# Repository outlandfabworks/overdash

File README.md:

# Overdash

Open-source digital dashboard for Raspberry Pi. Most commercial Pi-based dash solutions lock you into a single ECU brand and require paid third-party software licenses. Overdash doesn't: it speaks **J1939 CAN, OBD-II K-line, ELM327, CAN OBD, GPS, and GPIO** natively, so it works with engine swaps, custom builds, and vehicles that commercial options simply don't support.

A Python async backend reads from any combination of those sources simultaneously and streams everything over WebSocket to a Chromium kiosk frontend. Gauges are rendered on canvas, and the layout is fully editable in-browser with a visual no-code editor. No paid software required.

Built for a TDI-swapped Land Rover Discovery (J1939 engine + CompuShift Sport TCM + ZF4HP22EH), but config-driven; no code changes needed to adapt it to another vehicle.

---

## Features

- **Multiple data sources**: J1939 CAN, CompuShift TCM, OBD-II (K-line and ELM327), CAN OBD, Megasquirt/Speeduino USB serial, GPS (NMEA), analog ADC, frequency counter, GPIO inputs, and a mock source for development without hardware
- **Visual no-code layout editor**: drag to move, resize handles, properties panel for zones/thresholds/colors, gauge palette, theme picker, save to server or export JSON
- **Gauge types**: circular sweep (tach, speedo), vertical/horizontal bar, large numeric with value mapping, indicator lights, warning light strip with DTC panel
- **DTC monitoring**: Mode 03 (stored) + Mode 07 (pending) codes, MIL status, tap any active warning light to open the fault code panel
- **Odometer**: integrates vehicle speed into a persisted lifetime total and resettable trip counter
- **PWA**: add to home screen on a tablet for fullscreen landscape kiosk mode
- **Auth-protected HTTP API**: layout save/load, signal snapshot, trip reset, odometer set, per-source simulation mode

---

## Quick start

```bash
# Clone
git clone https://github.com/outlandfabworks/overdash.git
cd overdash

# Create a virtual environment and install dependencies
python3 -m venv .venv
.venv/bin/pip install -r requirements.txt

# Test with the mock vehicle source (no hardware required)
.venv/bin/python -m backend.main configs/vehicles/mock.yaml

# Open http://localhost:8080 in a browser
```

For full installation on a Raspberry Pi (CAN setup, systemd service, Chromium kiosk), see [INSTALL.md](INSTALL.md).

---

## Project structure

```
backend/
  main.py                     Entry point: wires sources, processors, servers
  data_bus.py                 In-memory signal store with asyncio pub/sub
  config.py                   YAML loader
  sources/
    base.py                   Abstract DataSource
    can_j1939.py              J1939 PGN/SPN decoder (python-can)
    can_compushift.py         CompuShift Sport TCM CAN messages
    can_obd.py                OBD-II over CAN (ISO 15765-4)
    obd_kline.py              ISO 9141-2 / KWP2000 K-line poller
    elm327.py                 ELM327 USB/Bluetooth OBD adapter
    megasquirt.py             Megasquirt 1/2/3 and Speeduino USB serial
    gps_nmea.py               GPS via NMEA serial stream
    analog_adc.py             Analog voltage/sensor via SPI ADC (MCP3xxx)
    frequency_counter.py      RPM/frequency via GPIO pulse counting
    gpio_inputs.py            Overdash Input HAT (turn signals, lights, reverse)
    mock_vehicle.py           Simulated signals for dev/testing
  processors/
    odometer.py               Integrates vehicle_speed → odometer + trip signals
  server/
    websocket.py              WebSocket broadcast server (30 Hz)
    http_api.py               HTTP API + frontend file serving (port 8080)

frontend/
  index.html                  Shell: loads layout, connects WebSocket
  manifest.json               PWA manifest (fullscreen, landscape)
  js/
    ws_client.js              WebSocket client with auto-reconnect
    layout.js                 CSS grid layout builder from JSON config
    gauge_registry.js         Plugin registry for gauge types
    gauges/
      base.js                 BaseGauge (canvas helpers, zone color lookup)
      circular.js             Circular/sweep gauge (tach, speedo)
      bar.js                  Vertical/horizontal bar gauge
      numeric.js              Large-number display with value_map support
      indicator.js            Single signal indicator light
      lights.js               Warning light strip with DTC panel
      light_icons.js          SVG icon definitions for warning lights
  editor/
    editor.js                 Visual layout editor (drag, resize, save)
    editor.css                Editor chrome and panel styles
    palette.js                Gauge palette sidebar
    properties.js             Gauge properties panel
    drag_grid.js              Grid snap and drag logic
  css/
    base.css                  Layout chrome, status bar
    themes/dark.css           Dark theme CSS variables
    themes/light.css          Light theme CSS variables

configs/
  vehicles/
    tdi_discovery.yaml        TDI Land Rover: J1939 + CompuShift + K-line
    generic_modern.yaml       Modern petrol/diesel: ELM327 or CAN OBD
    generic_obd2.yaml         Older OBD-II vehicle: K-line only
    offroad_expedition.yaml   Off-road build with GPS + ADC sensors
    mock.yaml                 Mock source: no hardware needed
  layouts/
    tdi_discovery.json        Default layout for the TDI Discovery

hardware/
  overdash-input-hat/          KiCad schematic and PCB for the GPIO input HAT
```

---

## Signal flow

```
Hardware  →  Source._read_loop()  →  DataBus.publish(name, value, unit)
                                           │
                                   OdometerProcessor (vehicle_speed → odometer/trip)
                                           │
                                   WebSocketServer (batches at 30 Hz)
                                           │
                                   Browser WSClient
                                           │
                                   LayoutManager.update(signals)
                                           │
                                   Gauge.draw(value)  →  <canvas>
```

---

## Adding a gauge type

1. Create `frontend/js/gauges/my_gauge.js` extending `BaseGauge`, implement `draw(value)`.
2. Register it in `index.html`: `GaugeRegistry.register('my_gauge', MyGauge)`.
3. Add a gauge entry in the layout JSON with `"type": "my_gauge"`.

## Adding a data source

1. Create `backend/sources/my_source.py` extending `BaseSource`, implement `_read_loop()`.
2. Register it in `backend/main.py`: `_SOURCE_TYPES['my_source'] = MySource`.
3. Add a source entry in the vehicle YAML with `type: my_source`.

---

## TDI Discovery: signal reference

| Signal | Source | Notes |
|--------|--------|-------|
| `engine_rpm` | J1939 PGN 61444 SPN 190 | EEC1 |
| `coolant_temp` | J1939 PGN 65262 | ET1 |
| `intake_map` | K-line PID 0x0B | Absolute kPa (doubles as boost) |
| `vehicle_speed` | J1939 PGN 65265 | CCVS1 |
| `trans_current_gear_label` | CompuShift CAN 0x3E0 | P/R/N/D/3/2/1 |
| `trans_tcc_lockup` | CompuShift CAN 0x3E0 | 0 = open, 1 = locked |
| `trans_temp` | CompuShift CAN 0x3E1 | °C |
| `battery_voltage` | J1939 PGN 65271 | VEP1 |
| `odometer` | Processor | Persisted lifetime km |
| `trip` | Processor | Resettable trip km |

## CompuShift Sport CAN IDs

Default map derived from community reverse-engineering (Sport firmware ≥ 2.x).
Override via `messages:` in the vehicle YAML if your TCM uses different IDs.

| CAN ID | Content |
|--------|---------|
| 0x3E0 | Current gear, target gear, TCC status, shift mode |
| 0x3E1 | Trans temp |
| 0x3E2 | Line pressure, error codes |

---

## License

MIT. See [LICENSE](LICENSE). Third-party license notices in [THIRD_PARTY_LICENSES.md](THIRD_PARTY_LICENSES.md).

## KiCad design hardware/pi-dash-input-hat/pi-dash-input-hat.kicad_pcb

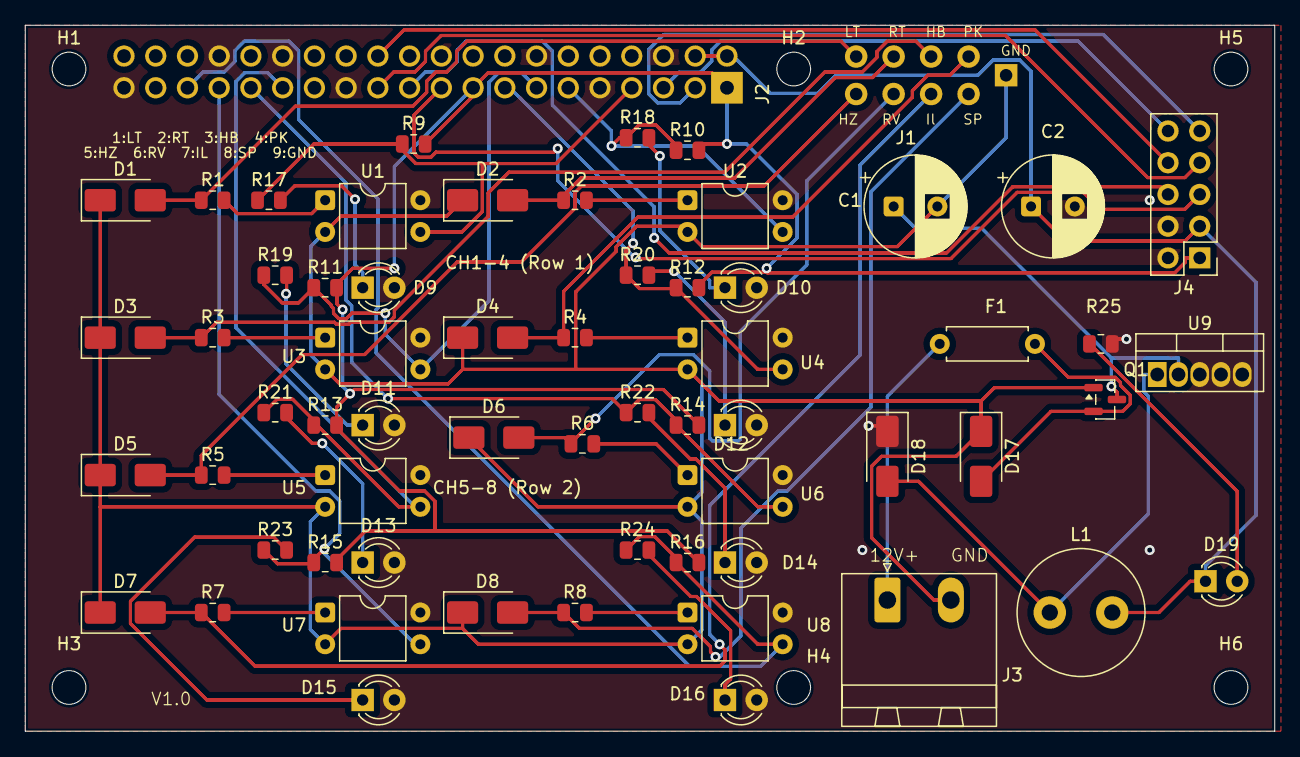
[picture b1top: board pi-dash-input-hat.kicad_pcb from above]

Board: 2 copper layers, 100.0 x 56.5 mm, 68 parts (0 on the bottom side), 47 nets.

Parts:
C1: 220u/35V; CP_Radial_D8.0mm_P3.50mm
C2: 220u/10V; CP_Radial_D8.0mm_P3.50mm
D1, D2, D3, D4, D5, D6, D7, D8: SMAJ15A; D_SMA
D9, D10, D11, D12, D13, D14, D15, D16, D19: LED_GRN; LED_D3.0mm
D17: SMAJ36A; D_SMA
D18: SB360; D_SMA
F1: 2.5A_Poly; R_Axial_DIN0207_L6.3mm_D2.5mm_P7.62mm_Horizontal
H1, H2, H3, H4, H5, H6: MountingHole_2.7mm_M2.5
J1: Molex_MicroFit3_9pin; PinHeader_1x09_P2.54mm_Vertical
J2: GPIO_2x20; PinHeader_2x20_P2.54mm_Vertical
J3: 12V_PWR_IN; PhoenixContact_MSTBA_2,5_2-G-5,08_1x02_P5.08mm_Horizontal
J4: Sensor_Connector; PinHeader_2x05_P2.54mm_Vertical
L1: 100u/3A; L_Radial_D10.0mm_P5.00mm_Fastron_07P
Q1: DMG2305UX; SOT-23
R1, R2, R3, R4, R5, R6, R7, R8: 560; R_0805_2012Metric
R9, R10, R11, R12, R13, R14, R15, R16: 10k; R_0805_2012Metric
R17, R18, R19, R20, R21, R22, R23, R24, R25: 1k; R_0805_2012Metric
U1, U2, U3, U4, U5, U6, U7, U8: PC817; DIP-4_W7.62mm
U9: LM2596-5.0; TO-220-5_Vertical

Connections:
12V_BATT: F1.1, J3.1
12V_CLEAN: D17.2, F1.2, Q1.2
+3V3: J2.1, J2.17, J4.1, R9.2, R10.2, R11.2, R12.2, R13.2, R14.2, R15.2, R16.2
+5V: C2.1, D19.1, J2.2, J2.4, J4.3, L1.2
CH1_LED: D9.1 (A), R17.2
CH1_MID: R1.2, U1.1 (A)
CH2_LED: D10.1 (A), R18.2
CH2_MID: R2.2, U2.1 (A)
CH3_LED: D11.1 (A), R19.2
CH3_MID: R3.2, U3.1 (A)
CH4_LED: D12.1 (A), R20.2
CH4_MID: R4.2, U4.1 (A)
CH5_LED: D13.1 (A), R21.2
CH5_MID: R5.2, U5.1 (A)
CH6_LED: D14.1 (A), R22.2
CH6_MID: R6.2, U6.1 (A)
CH7_LED: D15.1 (A), R23.2
CH7_MID: R7.2, U7.1 (A)
CH8_LED: D16.1 (A), R24.2
CH8_MID: R8.2, U8.1 (A)
GND: C2.2, D9.2 (K), D10.2 (K), D11.2 (K), D12.2 (K), D13.2 (K), D14.2 (K), D15.2 (K), D16.2 (K), D18.1, J2.6, J2.9, J2.14, J2.20, J2.25, J2.30, J2.34, J2.39, J4.2, J4.4, R25.2, U1.4 (E), U2.4 (E), U3.4 (E), U4.4 (E), U5.4 (E), U6.4 (E), U7.4 (E), U8.4 (E), U9.3, U9.4, U9.5
GND_CAR: C1.2, D1.1 (A), D2.1 (A), D3.1 (A), D4.1 (A), D5.1 (A), D6.1 (A), D7.1 (A), D8.1 (A), D17.1, J1.9, J3.2, Q1.1, U1.2 (K), U2.2 (K), U3.2 (K), U4.2 (K), U5.2 (K), U6.2 (K), U7.2 (K), U8.2 (K)
GPIO2: J2.3, J4.9
GPIO3: J2.5, J4.10
GPIO4: J2.7, R9.1, R17.1, U1.3 (C)
GPIO5: J2.29, R13.1, R21.1, U5.3 (C)
GPIO6: J2.31, R14.1, R22.1, U6.3 (C)
GPIO8: J2.24, J4.8
GPIO9: J2.21, J4.6
GPIO10: J2.19, J4.5
GPIO11: J2.23, J4.7
GPIO13: J2.33, R15.1, R23.1, U7.3 (C)
GPIO17: J2.11, R10.1, R18.1, U2.3 (C)
GPIO19: J2.35, R16.1, R24.1, U8.3 (C)
GPIO22: J2.15, R12.1, R20.1, U4.3 (C)
GPIO27: J2.13, R11.1, R19.1, U3.3 (C)
IN1_LT: D1.2 (K), J1.1, R1.1
IN2_RT: D2.2 (K), J1.2, R2.1
IN3_HB: D3.2 (K), J1.3, R3.1
IN4_PK: D4.2 (K), J1.4, R4.1
IN5_HZ: D5.2 (K), J1.5, R5.1
IN6_RV: D6.2 (K), J1.6, R6.1
IN7_IL: D7.2 (K), J1.7, R7.1
IN8_SP: D8.2 (K), J1.8, R8.1
LED_PWR: D19.2, R25.1
SW_NODE: D18.2, L1.1, U9.1
VIN_BUCK: C1.1, Q1.3, U9.2

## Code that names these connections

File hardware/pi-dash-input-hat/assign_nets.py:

import pcbnew

BOARD_FILE = '/home/zach/Documents/pi-dash/hardware/pi-dash-input-hat/pi-dash-input-hat.kicad_pcb'
board = pcbnew.LoadBoard(BOARD_FILE)

_net_cache = {}

def get_or_create_net(name):
    if name in _net_cache:
        return _net_cache[name]
    net = pcbnew.NETINFO_ITEM(board, name)
    board.Add(net)
    _net_cache[name] = net
    return net

def find_pad(fp, num):
    for pad in fp.Pads():
        if pad.GetNumber() == str(num):
            return pad
    return None

def assign(ref, pad_num, net_name):
    fp = board.FindFootprintByReference(ref)
    if not fp:
        print(f"FP not found: {ref}")
        return
    pad = find_pad(fp, pad_num)
    if not pad:
        print(f"Pad '{pad_num}' not found on {ref}")
        return
    pad.SetNet(get_or_create_net(net_name))

# Create all nets up front
for name in [
    'GND', 'GND_CAR', '+3V3', '+5V',
    'IN1_LT', 'IN2_RT', 'IN3_HB', 'IN4_PK',
    'IN5_HZ', 'IN6_RV', 'IN7_IL', 'IN8_SP',
    'GPIO4', 'GPIO5', 'GPIO6', 'GPIO13',
    'GPIO17', 'GPIO19', 'GPIO22', 'GPIO27',
    # Power section nets
    '12V_BATT', '12V_CLEAN', 'VIN_BUCK', 'SW_NODE', 'LED_PWR',
] + [f'CH{n}_MID' for n in range(1, 9)] \
  + [f'CH{n}_LED' for n in range(1, 9)]:
    get_or_create_net(name)

# Per-channel: D_TVS, R_560, U_PC817, R_pullup_10k, R_led_1k, D_LED, IN_net, GPIO_net
channels = [
    ('D1','R1', 'U1','R9', 'R17','D9',  'IN1_LT','GPIO4'),
    ('D2','R2', 'U2','R10','R18','D10', 'IN2_RT','GPIO17'),
    ('D3','R3', 'U3','R11','R19','D11', 'IN3_HB','GPIO27'),
    ('D4','R4', 'U4','R12','R20','D12', 'IN4_PK','GPIO22'),
    ('D5','R5', 'U5','R13','R21','D13', 'IN5_HZ','GPIO5'),
    ('D6','R6', 'U6','R14','R22','D14', 'IN6_RV','GPIO6'),
    ('D7','R7', 'U7','R15','R23','D15', 'IN7_IL','GPIO13'),
    ('D8','R8', 'U8','R16','R24','D16', 'IN8_SP','GPIO19'),
]

for i, (dn, rn, un, rpn, rln, dln, in_net, gpio) in enumerate(channels):
    ch   = i + 1
    mid  = f'CH{ch}_MID'
    led  = f'CH{ch}_LED'

    # TVS diode (SMAJ15A, D_SMA): pad 1 = A → car GND, pad 2 = K → input signal
    assign(dn, '1', 'GND_CAR')
    assign(dn, '2', in_net)

    # 560Ω input resistor (R_0805): pad 1 → input signal, pad 2 → opto input
    assign(rn, '1', in_net)
    assign(rn, '2', mid)

    # PC817 optocoupler (DIP-4):
    #   pin 1 A  → opto input (after R560)
    #   pin 2 K  → car GND
    #   pin 3 C  → GPIO / pull-up node
    #   pin 4 E  → Pi GND
    assign(un, '1', mid)
    assign(un, '2', 'GND_CAR')
    assign(un, '3', gpio)
    assign(un, '4', 'GND')

    # 10kΩ pull-up (R_0805): pad 1 → GPIO node, pad 2 → +3V3
    assign(rpn, '1', gpio)
    assign(rpn, '2', '+3V3')

    # 1kΩ LED resistor (R_0805): pad 1 → GPIO node, pad 2 → LED anode
    assign(rln, '1', gpio)
    assign(rln, '2', led)

    # Status LED (LED_D3.0mm): pad 1 A → LED anode, pad 2 K → Pi GND
    assign(dln, '1', led)
    assign(dln, '2', 'GND')

# J1 — 9-pin Molex: pads 1-8 = input signals, pad 9 = GND_CAR
for i, net in enumerate(['IN1_LT','IN2_RT','IN3_HB','IN4_PK',
                          'IN5_HZ','IN6_RV','IN7_IL','IN8_SP']):
    assign('J1', str(i + 1), net)
assign('J1', '9', 'GND_CAR')

# J2 — 2×20 Pi GPIO header (pad numbers = physical Pi pin numbers)
j2 = {
     1: '+3V3',   2: '+5V',    3: 'GPIO2',  4: '+5V',
     5: 'GPIO3',  6: 'GND',    7: 'GPIO4',  8: 'GPIO14',
     9: 'GND',   10: 'GPIO15', 11: 'GPIO17',12: 'GPIO18',
    13: 'GPIO27', 14: 'GND',   15: 'GPIO22',16: 'GPIO23',
    17: '+3V3',  18: 'GPIO24', 19: 'GPIO10',20: 'GND',
    21: 'GPIO9', 22: 'GPIO25', 23: 'GPIO11',24: 'GPIO8',
    25: 'GND',   26: 'GPIO7',  27: 'GPIO0', 28: 'GPIO1',
    29: 'GPIO5', 30: 'GND',   31: 'GPIO6', 32: 'GPIO12',
    33: 'GPIO13',34: 'GND',   35: 'GPIO19',36: 'GPIO16',
    37: 'GPIO26',38: 'GPIO20', 39: 'GND',  40: 'GPIO21',
}
for pad_num, net_name in j2.items():
    assign('J2', str(pad_num), net_name)

# ── Power section ─────────────────────────────────────────────────────────────
# J3 — 2-pin Phoenix screw terminal (12V input + GND_CAR)
assign('J3', '1', '12V_BATT')
assign('J3', '2', 'GND_CAR')

# F1 — series polyfuse (2.5A resettable)
assign('F1', '1', '12V_BATT')
assign('F1', '2', '12V_CLEAN')

# D17 — SMAJ36A TVS clamp (K on rail, A to car GND)
assign('D17', '1', 'GND_CAR')   # Anode
assign('D17', '2', '12V_CLEAN') # Cathode

# Q1 — DMG2305UX P-ch MOSFET reverse-polarity protection (SOT-23)
# Pad 1=G, 2=S, 3=D  (G→GND_CAR keeps MOSFET on; reversed polarity turns it off)
assign('Q1', '1', 'GND_CAR')    # Gate  → GND_CAR
assign('Q1', '2', '12V_CLEAN')  # Source → post-fuse rail
assign('Q1', '3', 'VIN_BUCK')   # Drain  → U9 VIN / C1 +

# C1 — 220µF/35V bulk input capacitor
assign('C1', '1', 'VIN_BUCK')   # +
assign('C1', '2', 'GND_CAR')    # −

# U9 — LM2596-5.0 buck converter (TO-220-5)
# Physical LM2596 pins: 1=OUT(switch), 2=VIN, 3=GND, 4=FB(fixed), 5=/ON-OFF
assign('U9', '1', 'SW_NODE')    # Switch output
assign('U9', '2', 'VIN_BUCK')   # VIN
assign('U9', '3', 'GND')        # GND (also exposed tab)
assign('U9', '4', 'GND')        # FB fixed internally; tie /ON-OFF to GND = always on
assign('U9', '5', 'GND')        # /ON-OFF → GND (always enabled)

# D18 — SB360 Schottky freewheeling diode (K toward switch node, A to GND)
assign('D18', '1', 'GND')       # Anode
assign('D18', '2', 'SW_NODE')   # Cathode → switch node

# L1 — 100µH/3A output inductor
assign('L1', '1', 'SW_NODE')    # pin 1 → switch node
assign('L1', '2', '+5V')        # pin 2 → +5V output

# C2 — 220µF/10V output filter capacitor
assign('C2', '1', '+5V')        # +
assign('C2', '2', 'GND')        # −

# D19 — green power LED (A→+5V, K→LED_PWR node)
assign('D19', '1', '+5V')       # Anode
assign('D19', '2', 'LED_PWR')   # Cathode → R25

# R25 — 1kΩ LED current limiter
assign('R25', '1', 'LED_PWR')   # → D19 cathode
assign('R25', '2', 'GND')       # → GND

board.Save(BOARD_FILE)
print("Done — all pads assigned, ratsnest ready.")

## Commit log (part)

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2026-06-08 Initial release — modular Raspberry Pi digital dashboard Python asyncio backend with pluggable data sources (J1939, CompuShift, OBD-II K-line, ELM327, CAN OBD, GPS, ADC, GPIO); canvas-based frontend 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
2026-06-09 Sharpen README intro to highlight open-source differentiators
2026-06-09 Replace em dashes with standard punctuation in README
2026-06-09 Add Megasquirt/Speeduino USB serial source Implements the MS Serial protocol ('A' command real-time data block). Supports MS1 (9600 baud, 22-byte frame), MS2Extra / MS3 (115200 baud), and Speeduino (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
2026-06-11 Fix missing time import in odometer processor The odometer's stale-reading check called time.time() without importing the time module, raising a NameError as soon as vehicle_speed was published. Sinc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
